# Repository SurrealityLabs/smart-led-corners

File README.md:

# smart-led-corners
For making smart LED strips turn 90 degrees

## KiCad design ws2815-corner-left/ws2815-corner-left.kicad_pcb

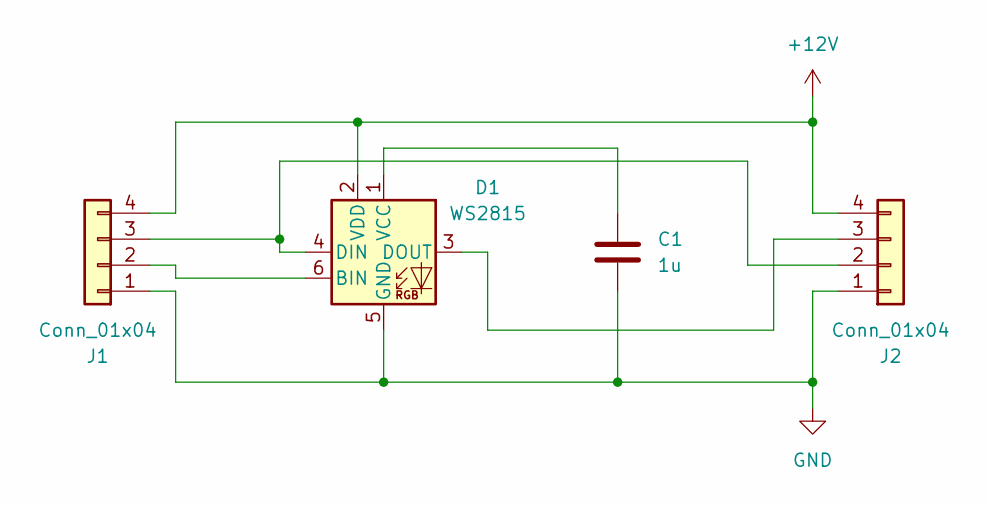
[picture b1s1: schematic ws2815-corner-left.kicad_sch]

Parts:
C1: 1u; C_0603_1608Metric; LCSC C15849
D1: WS2815; LED_WS2812_PLCC6_5.0x5.0mm_P1.6mm
J1: Conn_01x04; strip_begin_2815
J2: Conn_01x04; strip_end_2815

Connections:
+12V: D1.2 (VDD), J1.4, J2.4
GND: C1.2, D1.5 (GND), J1.1, J2.1
unnamed: D1.6 (BIN), J1.2
unnamed: D1.4 (DIN), J1.3, J2.2
unnamed: D1.3 (DOUT), J2.3
unnamed: C1.1, D1.1 (VCC)

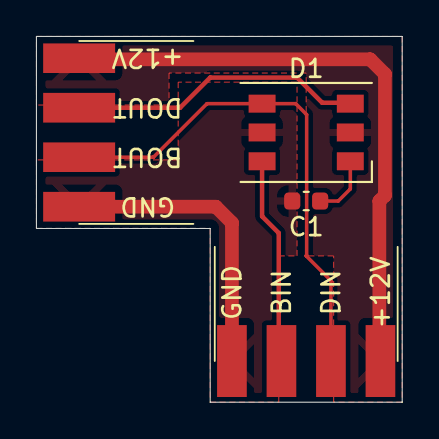
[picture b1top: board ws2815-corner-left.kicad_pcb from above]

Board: 2 copper layers, 20.3 x 20.3 mm, 4 parts (0 on the bottom side), 6 nets.

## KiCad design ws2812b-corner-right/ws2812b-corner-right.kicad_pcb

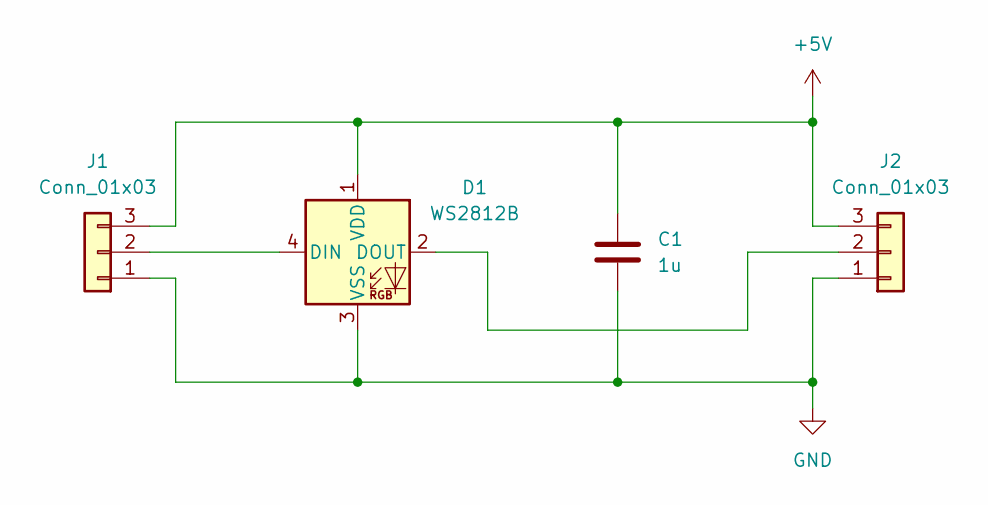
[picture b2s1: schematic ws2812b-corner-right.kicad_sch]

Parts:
C1: 1u; C_0603_1608Metric; LCSC C15849
D1: WS2812B; LED_WS2812B_PLCC4_5.0x5.0mm_P3.2mm; LCSC C2843785
J1: Conn_01x03; strip_begin
J2: Conn_01x03; strip_end

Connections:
+5V: C1.1, D1.1 (VDD), J1.3, J2.3
GND: C1.2, D1.3 (VSS), J1.1, J2.1
unnamed: D1.4 (DIN), J1.2
unnamed: D1.2 (DOUT), J2.2

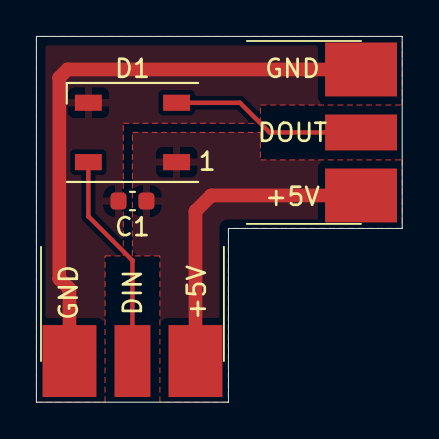
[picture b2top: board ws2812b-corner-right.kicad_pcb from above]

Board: 2 copper layers, 20.3 x 20.3 mm, 4 parts (0 on the bottom side), 4 nets.

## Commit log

2024-08-30 Adding WS2812B corners and WS2815 corner
